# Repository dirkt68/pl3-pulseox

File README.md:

# Project Lab 3
## Digital Communications Project Lab

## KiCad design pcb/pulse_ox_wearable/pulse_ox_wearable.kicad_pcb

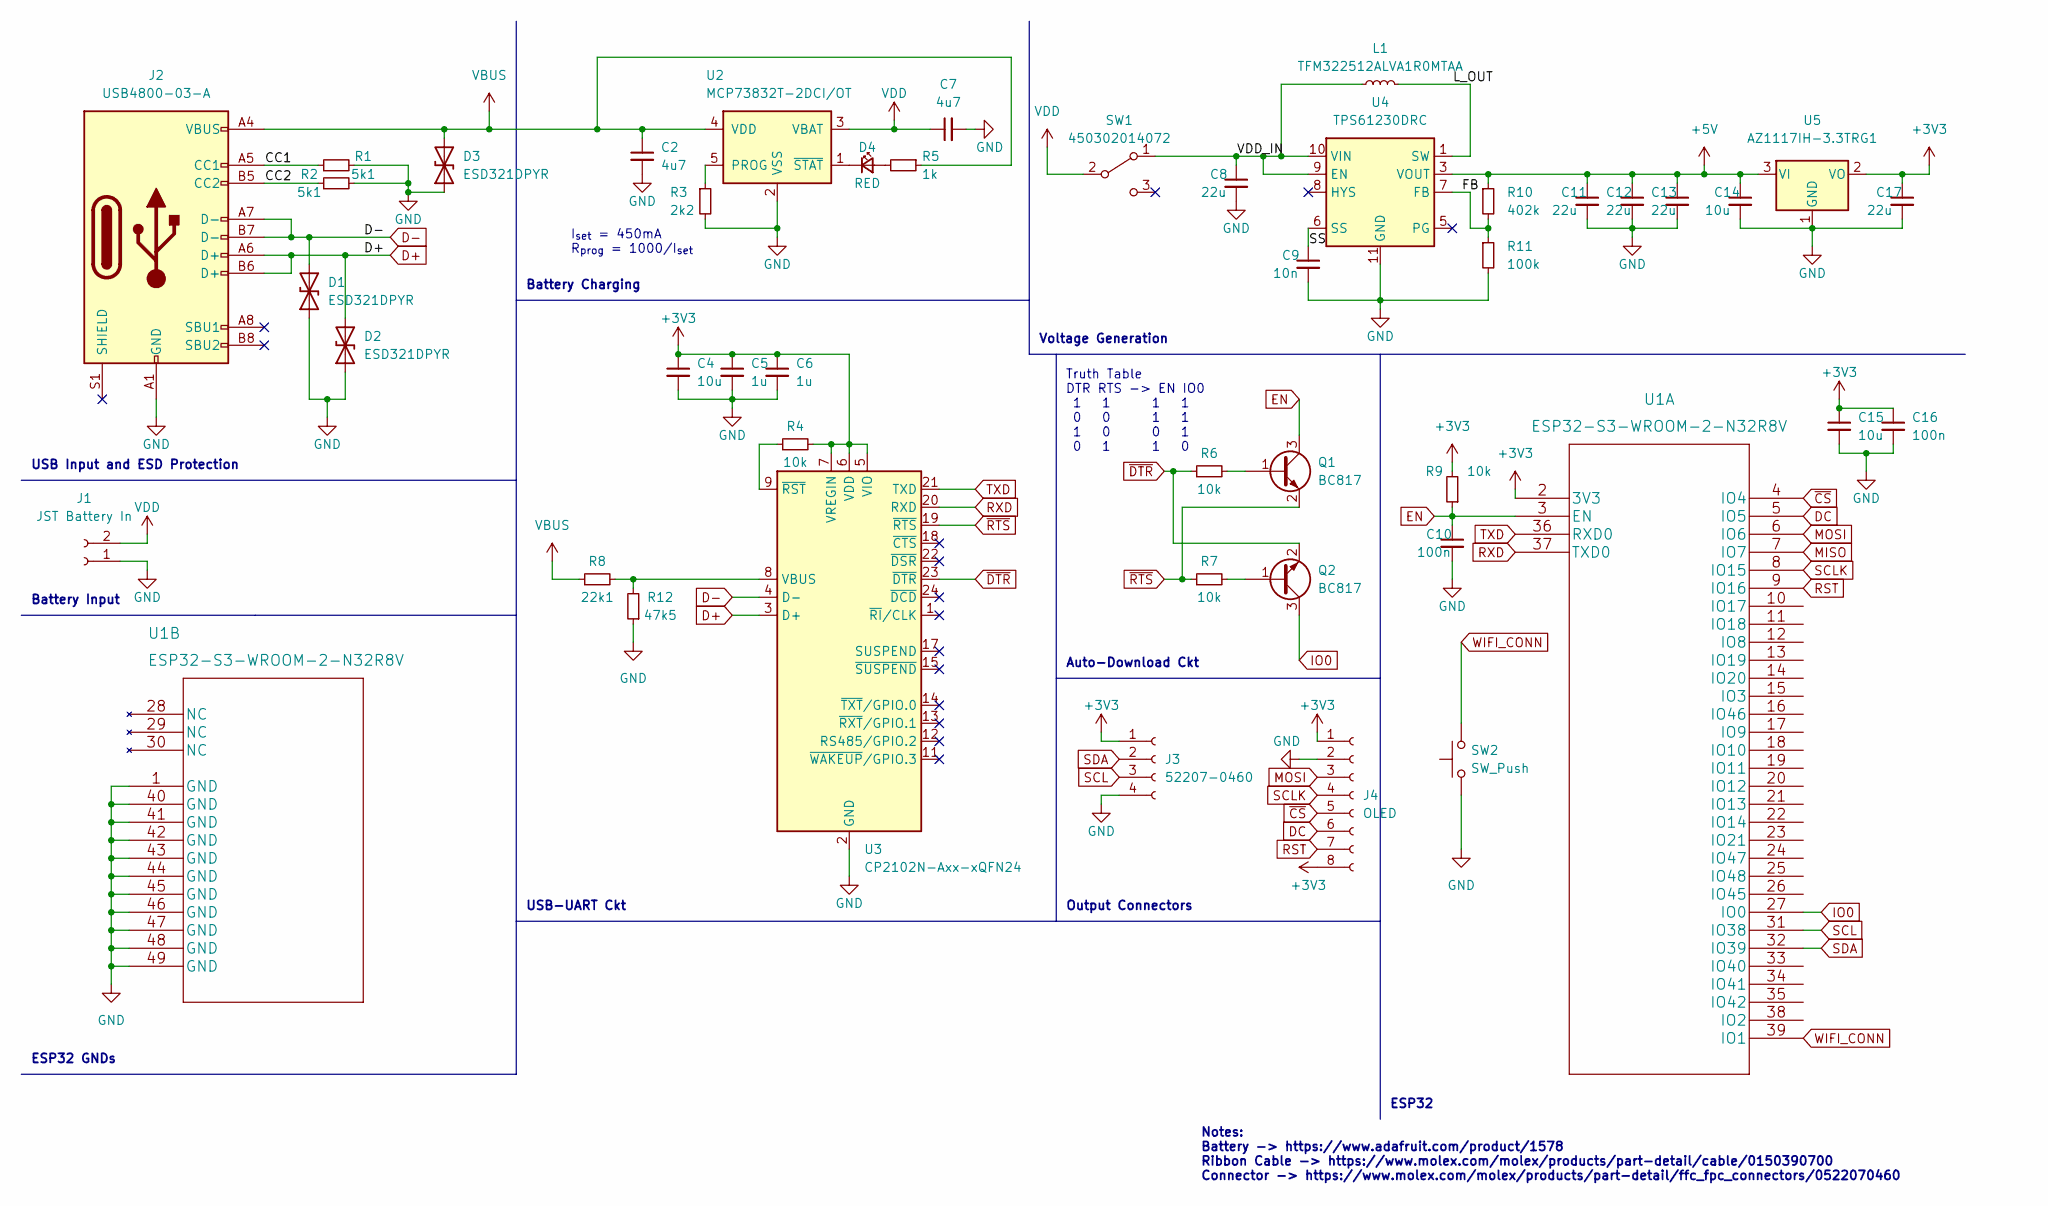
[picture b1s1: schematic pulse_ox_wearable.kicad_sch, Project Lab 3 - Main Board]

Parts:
C2, C7: 4u7; C_0603_1608Metric
C4, C14, C15: 10u; C_0805_2012Metric
C5, C6: 1u; C_0805_2012Metric
C8, C11, C12, C13, C17: 22u; C_1206_3216Metric
C9: 10n; C_0201_0603Metric
C10, C16: 100n; C_0603_1608Metric
D1, D2, D3: ESD321DPYR; D_0402_1005Metric
D4: RED; LED_0603_1608Metric
J1: JST Battery In; JST_PH_B2B-PH-K_1x02_P2.00mm_Vertical
J2: USB4800-03-A; USB_C_Receptacle_HRO_TYPE-C-31-M-12
J3: 52207-0460; 0522070433
J4: OLED; PinHeader_1x08_P2.54mm_Vertical
L1: TFM322512ALVA1R0MTAA; L_1210_3225Metric
Q1, Q2: BC817; SOT-23
R1, R2: 5k1; R_0201_0603Metric
R3: 2k2; R_0201_0603Metric
R4, R6, R7, R9: 10k; R_1210_3225Metric
R5: 1k; R_0805_2012Metric
R8: 22k1; R_0402_1005Metric
R10: 402k; R_0603_1608Metric
R11: 100k; R_0603_1608Metric
R12: 47k5; R_0402_1005Metric
SW1: 450302014072; SS12D00(SPDT amazon)
SW2: SW_Push; SW_SPST_B3U-1000P
U1: ESP32-S3-WROOM-2-N32R8V
U2: MCP73832T-2DCI/OT; SOT-23-5
U3: CP2102N-Axx-xQFN24; QFN-24-1EP_4x4mm_P0.5mm_EP2.6x2.6mm
U4: TPS61230DRC; Texas_S-PVSON-N10_ThermalVias
U5: AZ1117IH-3.3TRG1; SOT-223

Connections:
+3V3: C4.1, C5.1, C6.1, C15.1, C16.1, C17.1, J3.1, J4.1, J4.8, R4.2, R9.2, U1.2 (3V3), U3.5 (VIO), U3.6 (VDD), U3.7 (VREGIN), U5.2 (VO)
+5V: C11.1, C12.1, C13.1, C14.1, R10.1, U4.3 (VOUT), U4.4 (VOUT), U5.3 (VI)
/CC1: J2.A5 (CC1), R1.1
/CC2: J2.B5 (CC2), R2.1
/FB: R10.2, R11.1, U4.7 (FB)
/L_OUT: L1.2, U4.1 (SW), U4.2 (SW)
/SS: C9.1, U4.6 (SS)
/VDD_IN: C8.1, L1.1, SW1.1 (A), U4.9 (EN), U4.10 (VIN)
D+: D2.2 (A2), J2.A6 (D+), J2.B6 (D+), U3.3 (D+)
D-: D1.2 (A2), J2.A7 (D-), J2.B7 (D-), U3.4 (D-)
DC: J4.6, U1.5 (IO5)
EN: C10.1, Q1.3 (C), R9.1, U1.3 (EN)
GND: C2.2, C4.2, C5.2, C6.2, C7.2, C8.2, C9.2, C10.2, C11.2, C12.2, C13.2, C14.2, C15.2, C16.2, C17.2, D1.1 (A1), D2.1 (A1), D3.1 (A1), J1.1, J2.A1 (GND), J2.A12 (GND), J2.B1 (GND), J2.B12 (GND), J3.4, J4.2, R1.2, R2.2, R3.2, R11.2, R12.1, SW2.1, U1.1 (GND), U1.40 (GND), U1.41 (GND), U1.42 (GND), U1.43 (GND), U1.44 (GND), U1.45 (GND), U1.46 (GND), U1.47 (GND), U1.48 (GND), U1.49 (GND), U2.2 (VSS), U3.2 (GND), U3.25 (GND), U4.11 (GND), U5.1 (GND)
IO0: Q2.3 (C), U1.27 (IO0)
MISO: U1.7 (IO7)
MOSI: J4.3, U1.6 (IO6)
unnamed: D4.2 (A), R5.2
unnamed: D4.1 (K), U2.1 (~STAT)
unnamed: Q1.1 (B), R6.2
unnamed: Q2.1 (B), R7.2
unnamed: R3.1, U2.5 (PROG)
unnamed: R8.2, R12.2, U3.8 (VBUS)
unnamed: R4.1, U3.9 (~RST)
RST: J4.7, U1.9 (IO16)
RXD: U1.37 (TXD0), U3.20 (RXD)
SCL: J3.3, U1.31 (IO38)
SCLK: J4.4, U1.8 (IO15)
SDA: J3.2, U1.32 (IO39)
TXD: U1.36 (RXD0), U3.21 (TXD)
VBUS: C2.1, D3.2 (A2), J2.A4 (VBUS), J2.A9 (VBUS), J2.B4 (VBUS), J2.B9 (VBUS), R5.1, R8.1, U2.4 (VDD)
VDD: C7.1, J1.2, SW1.2 (B), U2.3 (VBAT)
WIFI_CONN: SW2.2, U1.39 (IO1)
~CS: J4.5, U1.4 (IO4)
~DTR: Q2.2 (E), R6.1, U3.23 (~DTR)
~RTS: Q1.2 (E), R7.1, U3.19 (~RTS)

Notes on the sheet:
I_{set} = 450mA R_{prog} = 1000/I_{set}
Voltage Generation
Battery Input
Truth Table DTR RTS -> EN IO0 1 1 1 1 0 0 1 1 1 0 0 1 0 1 1 0
USB-UART Ckt
ESP32
USB Input and ESD Protection
Battery Charging
Notes: Battery -> https://www.adafruit.com/product/1578 Ribbon Cable -> https://www.molex.com/molex/products/part-detail/cable/0150390700 Connector -> https://www.molex.com/molex/products/part-detail/ffc_fpc_connectors/0522070460
ESP32 GNDs
Output Connectors
Auto-Download Ckt

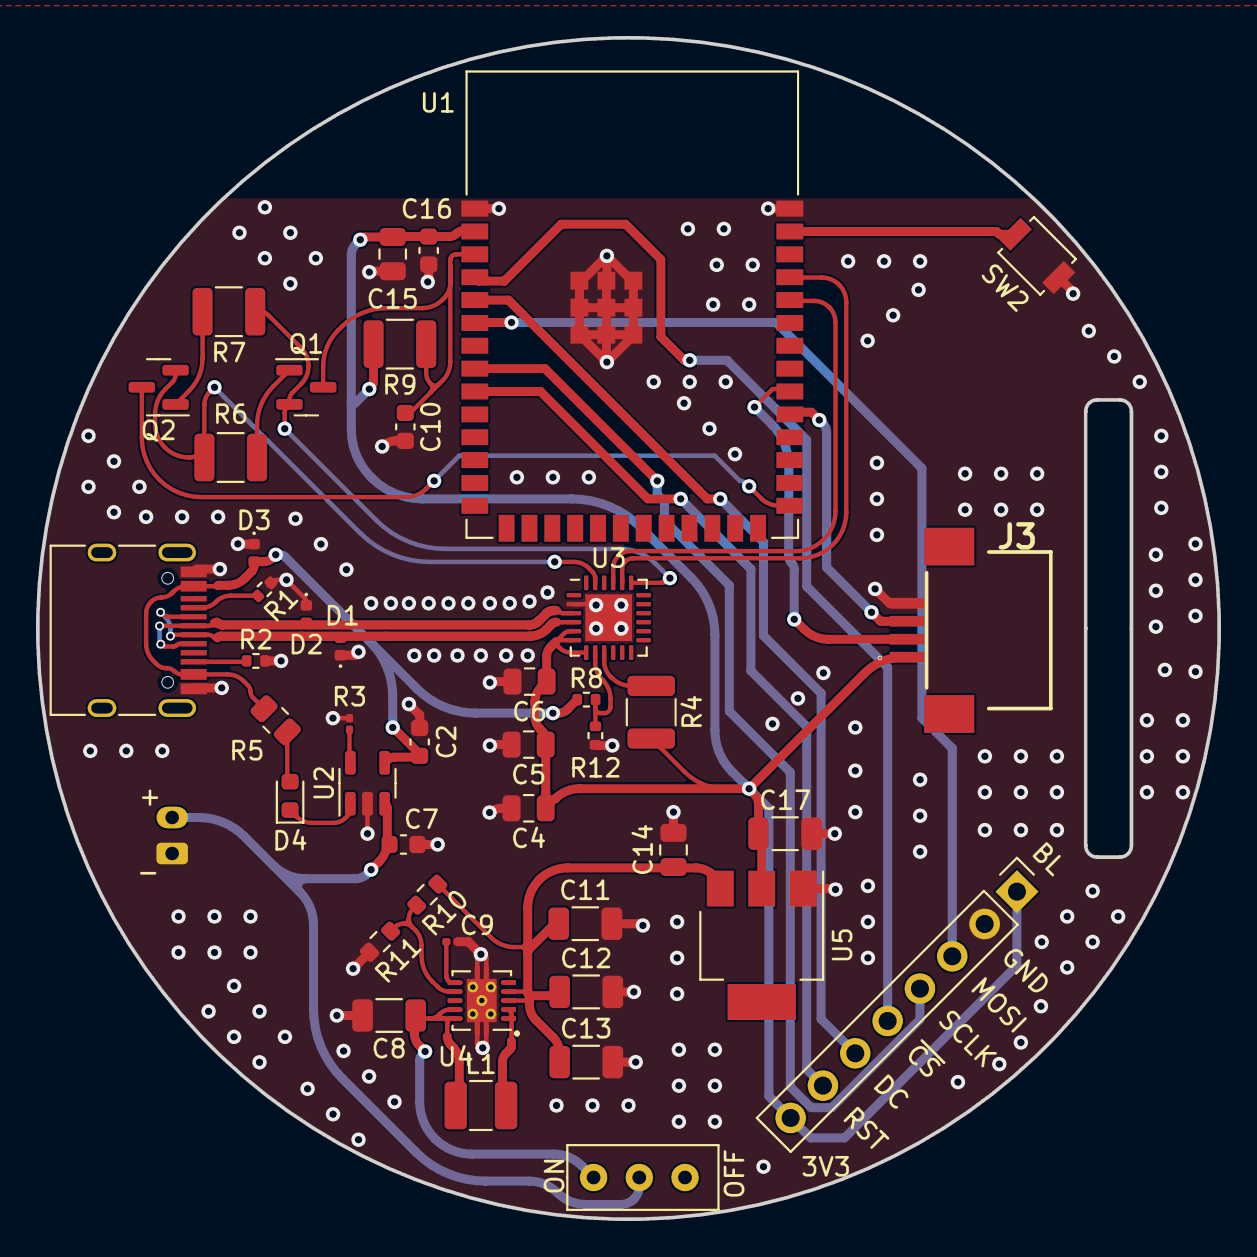
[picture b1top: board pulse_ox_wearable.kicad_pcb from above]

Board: 4 copper layers, 65.6 x 65.6 mm, 45 parts (1 on the bottom side), 34 nets.

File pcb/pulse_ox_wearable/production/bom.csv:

Designator,Footprint,Quantity,Value,LCSC Part #
C10,0603,1,100n,
C11,1206,1,22u,
C12,1206,1,22u,
C13,1206,1,22u,
C14,0805,1,10u,
C15,0805,1,10u,
C16,0603,1,100n,
C17,1206,1,22u,
C2,0603,1,4u7,
C4,0805,1,10u,
C5,0805,1,1u,
C6,0805,1,1u,
C7,0603,1,4u7,
C8,1206,1,22u,
C9,0201,1,10n,
D1,0402,1,ESD321DPYR,
D2,0402,1,ESD321DPYR,
D3,0402,1,ESD321DPYR,
D4,0603,1,RED,
I2C,0522070433,1,52207-0460 ,
J1,JST_PH_B2B-PH-K_1x02_P2.00mm_Vertical,1,JST Battery In,
J2,USB_C_Receptacle_HRO_TYPE-C-31-M-12,1,USB4800-03-A,
J4,PinHeader_1x08_P2.54mm_Vertical,1,OLED,
L1,L_SMD_4.8_x_2.85,1,XFL4020-102MEB,
"Q1, Q2",SOT-23,2,BC817,
R1,0201,1,5k1,
R10,0603,1,402k,
R11,0603,1,100k,
R12,0402,1,47k5,
R2,0201,1,5k1,
R3,0201,1,2k2,
R4,1210,1,10k,
R5,0805,1,1k,
R6,1210,1,10k,
R7,1210,1,10k,
R8,0402,1,22k1,
R9,1210,1,10k,
SW1,SS12D00(SPDT amazon),1,450302014072 ,
SW2,SW_SPST_B3U-1000P,1,SW_Push,
U1,ESP32-S3-WROOM-2-N32R8V,1,ESP32-S3-WROOM-2-N32R8V,
U2,SOT-23-5,1,MCP73832T-2DCI/OT,
U3,QFN-24-1EP_4x4mm_P0.5mm_EP2.6x2.6mm,1,CP2102N-Axx-xQFN24,
U4,Texas_S-PVSON-N10_ThermalVias,1,TPS61230DRC,
U5,SOT-223,1,AZ1117IH-3.3TRG1,

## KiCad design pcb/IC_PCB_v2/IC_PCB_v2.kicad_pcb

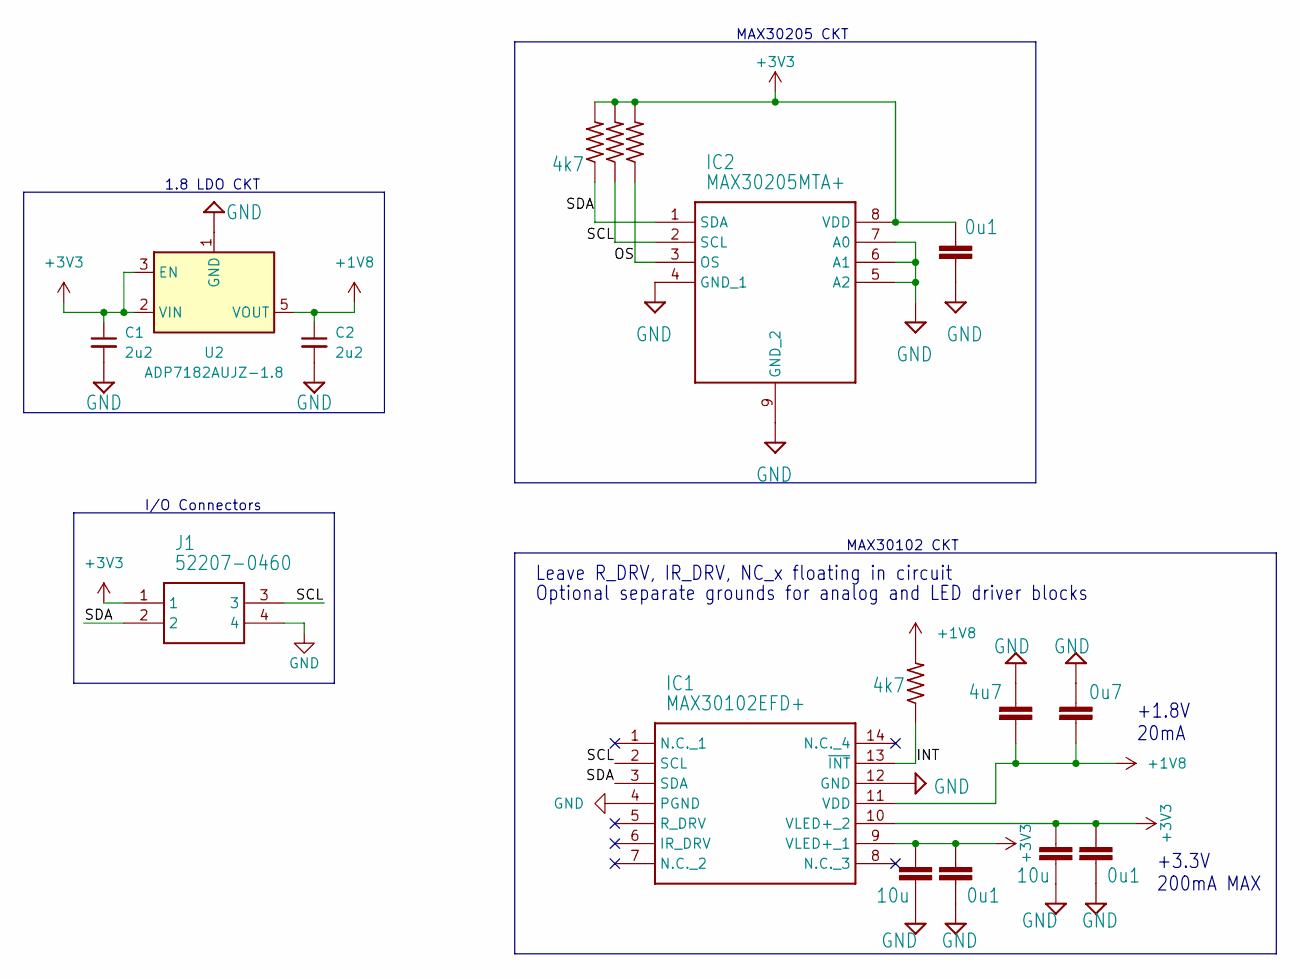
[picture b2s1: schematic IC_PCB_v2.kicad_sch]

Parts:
C1, C2: 2u2; C_0603_1608Metric
C3, C7: 10u; C_0603_1608Metric
C4, C5, C9: 0u1; C_0201_0603Metric_Pad0.64x0.40mm_HandSolder
C6: 4u7; C_0201_0603Metric_Pad0.64x0.40mm_HandSolder
C8: 0u7; C_0201_0603Metric_Pad0.64x0.40mm_HandSolder
IC1: MAX30102EFD+; 14-LEAD-OESIP
IC2: MAX30205MTA+; SON65P300X300X80-9N
J1: 52207-0460; 0522070433
R3, R4: 4.7k; R_0201_0603Metric_Pad0.64x0.40mm_HandSolder
R5, R6: 4k7; R_0201_0603Metric_Pad0.64x0.40mm_HandSolder
U2: ADP7182AUJZ-1.8; TSOT-23-5

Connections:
+1V8: C2.1, C6.2, C8.2, IC1.11 (VDD), R6.2, U2.5 (VOUT)
+3V3: C1.1, C3.1, C4.1, C5.1, C7.1, C9.1, IC1.9 (VLED+_1), IC1.10 (VLED+_2), IC2.8 (VDD), J1.1, R3.2, R4.2, R5.2, U2.2 (VIN), U2.3 (EN)
/INT: IC1.13 (~INT), R6.1
/OS: IC2.3 (OS), R5.1
/SCL: IC1.2 (SCL), IC2.2 (SCL), J1.3, R4.1
/SDA: IC1.3 (SDA), IC2.1 (SDA), J1.2, R3.1
GND: C1.2, C2.2, C3.2, C4.2, C5.2, C6.1, C7.2, C8.1, C9.2, IC1.4 (PGND), IC1.12 (GND), IC2.4 (GND_1), IC2.5 (A2), IC2.6 (A1), IC2.7 (A0), IC2.9 (GND_2), J1.4, U2.1 (GND)

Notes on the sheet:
+3.3V 200mA MAX
1.8 LDO CKT
+1.8V 20mA
Optional separate grounds for analog and LED driver blocks
MAX30102 CKT
MAX30205 CKT
I/O Connectors
Leave R_DRV, IR_DRV, NC_x floating in circuit

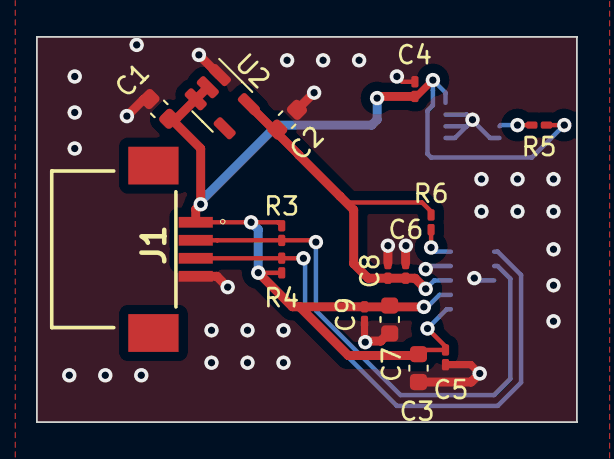
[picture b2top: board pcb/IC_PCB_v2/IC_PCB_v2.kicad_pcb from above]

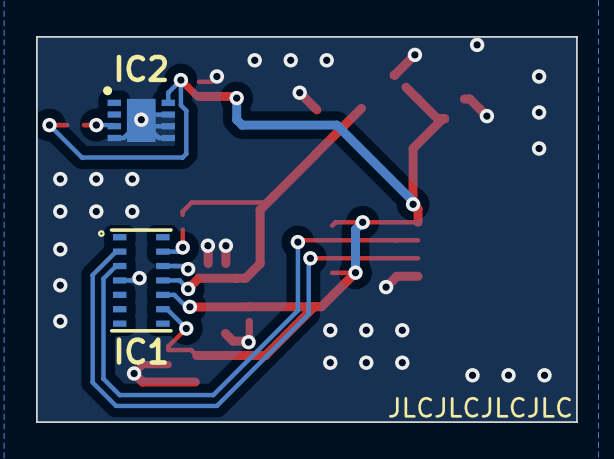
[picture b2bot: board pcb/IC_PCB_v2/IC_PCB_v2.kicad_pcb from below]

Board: 2 copper layers, 30.0 x 21.4 mm, 17 parts (2 on the bottom side), 7 nets.

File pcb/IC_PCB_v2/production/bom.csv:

Designator,Footprint,Quantity,Value,LCSC Part #
C1,0603,1,2u2,
C2,0603,1,2u2,
C3,0603,1,10u,
C4,0201,1,0u1,
C5,0201,1,0u1,
C6,0201,1,4u7,
C7,0603,1,10u,
C8,0201,1,0u7,
C9,0201,1,0u1,
IC1,14-LEAD-OESIP,1,MAX30102EFD+,
IC2,SON65P300X300X80-9N,1,MAX30205MTA+,
J1,0522070433,1,52207-0460,
R3,0201,1,4.7k,
R4,0201,1,4.7k,
R5,0201,1,4k7,
R6,0201,1,4k7,
U2,TSOT-23-5,1,ADP7182AUJZ-1.8,

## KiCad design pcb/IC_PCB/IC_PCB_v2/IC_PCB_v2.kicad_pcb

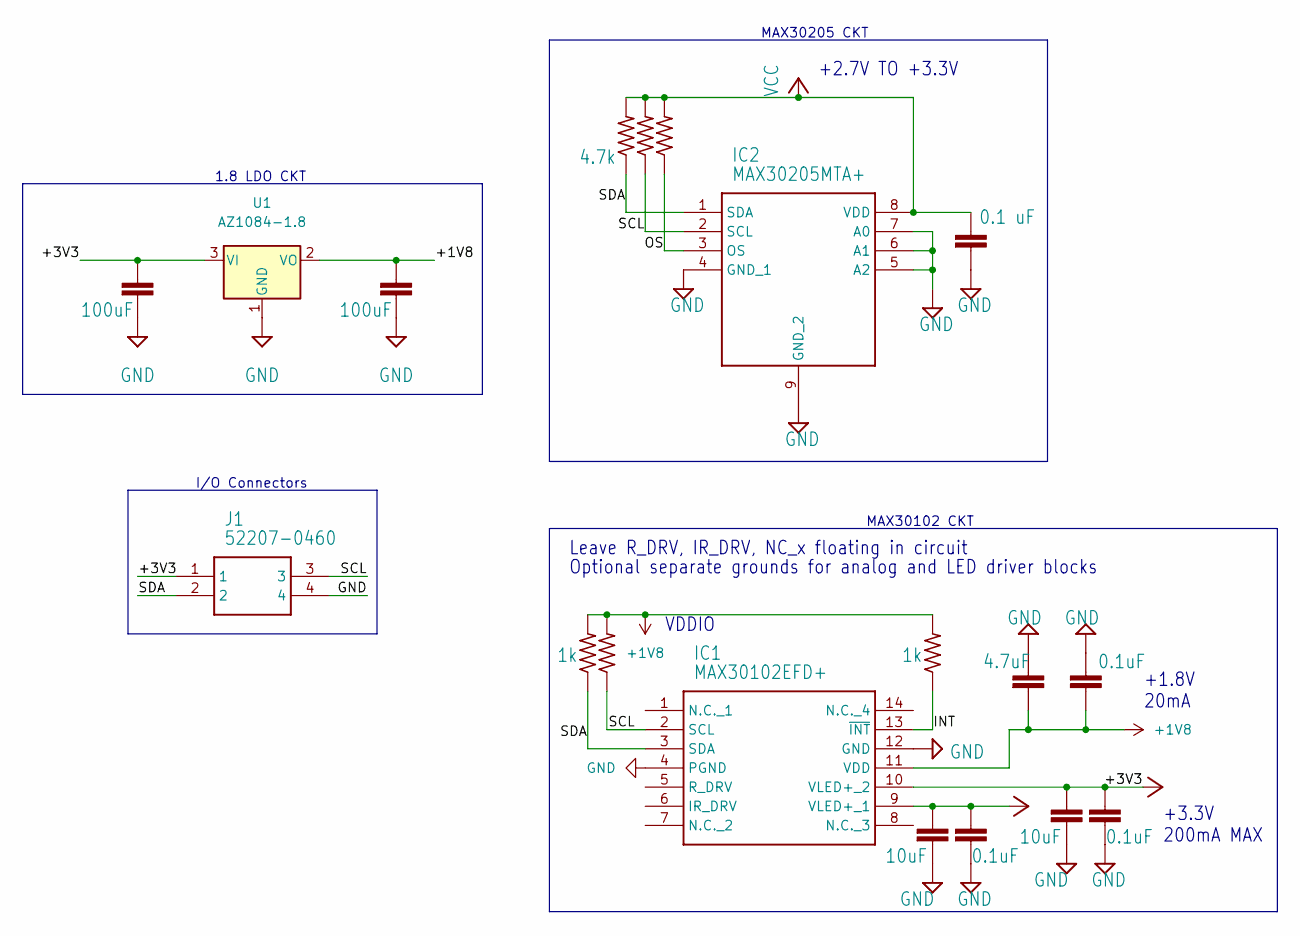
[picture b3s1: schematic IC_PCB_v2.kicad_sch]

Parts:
C1, C2: 100uF; C_0201_0603Metric_Pad0.64x0.40mm_HandSolder
C3, C7: 10uF; C_0201_0603Metric_Pad0.64x0.40mm_HandSolder
C4: 0.1 uF; C_0201_0603Metric_Pad0.64x0.40mm_HandSolder
C5, C8, C9: 0.1uF; C_0201_0603Metric_Pad0.64x0.40mm_HandSolder
C6: 4.7uF; C_0201_0603Metric_Pad0.64x0.40mm_HandSolder
IC1: MAX30102EFD+; 14-LEAD-OESIP
IC2: MAX30205MTA+; SON65P300X300X80-9N
J1: 52207-0460; 0522070433
R1, R2, R6: 1k; R_0201_0603Metric_Pad0.64x0.40mm_HandSolder
R3, R4, R5: 4.7k; R_0201_0603Metric_Pad0.64x0.40mm_HandSolder
U1: AZ1084-1.8; TO-252-3_TabPin2

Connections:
+1V8: C2.1, C6.2, C8.2, IC1.11 (VDD), R1.2, R2.2, R6.2, U1.2 (VO)
/INT: IC1.13 (~INT), R6.1
/OS: IC2.3 (OS), R5.1
/SCL: IC1.2 (SCL), IC2.2 (SCL), J1.3, R2.1, R4.1
/SDA: IC1.3 (SDA), IC2.1 (SDA), J1.2, R1.1, R3.1
GND: C1.2, C2.2, C3.2, C4.2, C5.2, C6.1, C7.2, C8.1, C9.2, IC1.4 (PGND), IC1.12 (GND), IC2.4 (GND_1), IC2.5 (A2), IC2.6 (A1), IC2.7 (A0), IC2.9 (GND_2), J1.4, U1.1 (GND)
VCC: C1.1, C3.1, C4.1, C5.1, C7.1, C9.1, IC1.9 (VLED+_1), IC1.10 (VLED+_2), IC2.8 (VDD), J1.1, R3.2, R4.2, R5.2, U1.3 (VI)

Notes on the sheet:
+3.3V 200mA MAX
VDDIO
1.8 LDO CKT
+1.8V 20mA
Optional separate grounds for analog and LED driver blocks
MAX30102 CKT
MAX30205 CKT
I/O Connectors
Leave R_DRV, IR_DRV, NC_x floating in circuit
+2.7V TO +3.3V

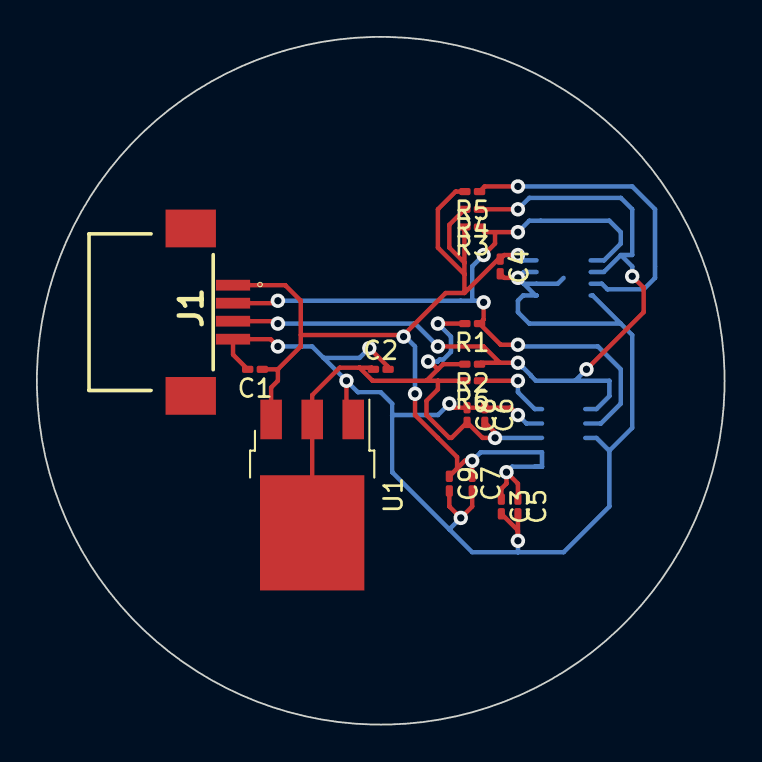
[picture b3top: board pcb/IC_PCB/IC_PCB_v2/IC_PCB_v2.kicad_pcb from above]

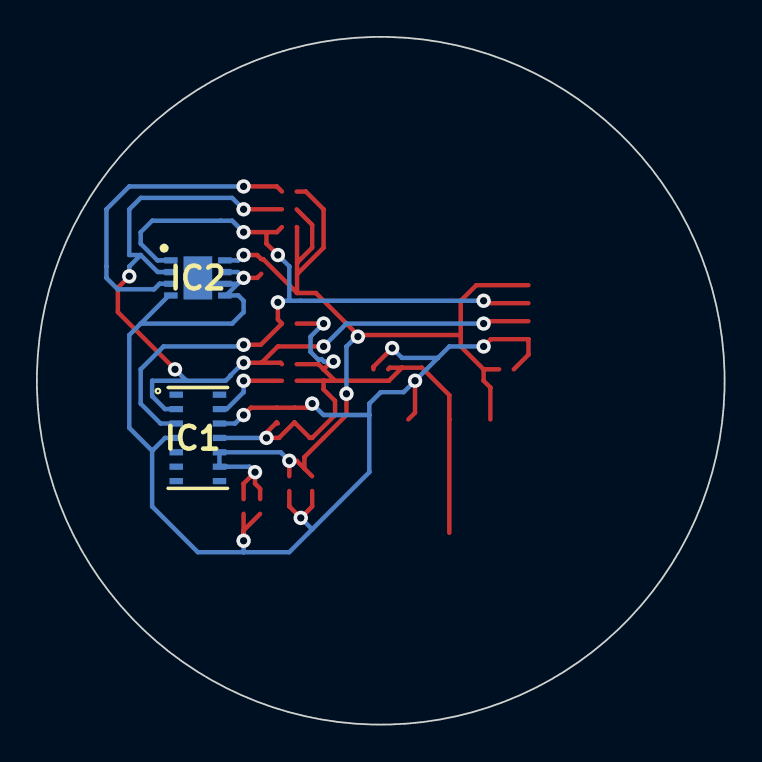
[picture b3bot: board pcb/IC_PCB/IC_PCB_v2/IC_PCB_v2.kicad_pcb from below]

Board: 2 copper layers, 38.2 x 38.2 mm, 19 parts (2 on the bottom side), 7 nets.

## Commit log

2023-01-12 First push with some initial data
2023-02-01 initialized repo
2023-02-06 added daughter PCB to git repo
2023-02-08 updated for week 4
2023-02-22 uploaded code and stuff
2023-04-01 updating
2023-04-12 Pushed some stuff
2023-04-12 display code
2023-04-24 display code final
2023-04-24 pushed some code
2023-04-24 integrated display
2023-04-24 added missing folder
2023-04-24 changed user setup
2023-04-24 modified logo
2023-04-24 added website code, moved folders
2023-04-29 added ring to display
2023-05-05 probably final push
2023-05-05 one more

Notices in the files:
parts and their libraries:
Copyright 2021 Accelerated Designs. All rights reserved.
